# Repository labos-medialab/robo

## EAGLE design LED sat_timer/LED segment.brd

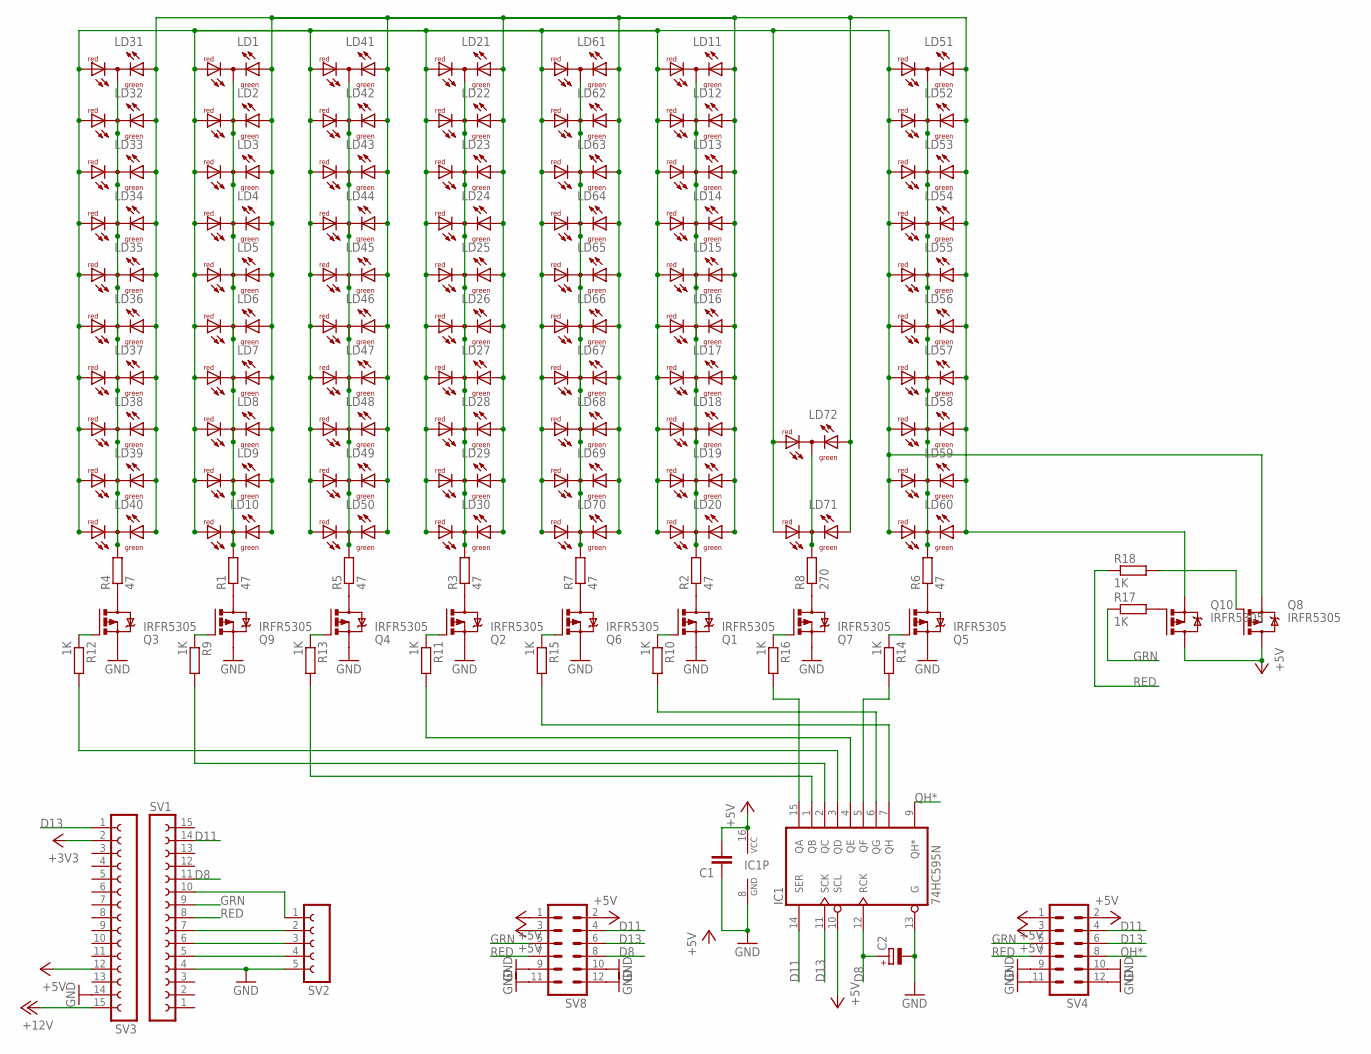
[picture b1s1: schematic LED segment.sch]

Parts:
C1: C-EU050-030X075; C050-030X075
C2: CPOL-EUE2.5-7; E2,5-7
IC1: 74HC595N; DIL16
LD1, LD2, LD3, LD4, LD5, LD6, LD7, LD8, LD9, LD10, LD11, LD12, LD13, LD14, LD15, LD16, LD17, LD18, LD19, LD20, LD21, LD22, LD23, LD24, LD25, LD26, LD27, LD28, LD29, LD30, LD31, LD32, LD33, LD34, LD35, LD36, LD37, LD38, LD39, LD40, LD41, LD42, LD43, LD44, LD45, LD46, LD47, LD48, LD49, LD50, LD51, LD52, LD53, LD54, LD55, LD56, LD57, LD58, LD59, LD60, LD61, LD62, LD63, LD64, LD65, LD66, LD67, LD68, LD69, LD70, LD71, LD72: DUOLED-RG-C; DUOLED-C-5MM
Q1, Q2, Q3, Q4, Q5, Q6, Q7, Q8, Q9, Q10: IRFR5305; D-PAK_TO252AA
R1, R2, R3, R4, R5, R6: 47; 0204/7
R7: 47; 0207/5V
R8: 270; 0204/7
R9, R10, R11, R12, R13, R14, R15, R16, R17, R18: 1K; 0204/7
SV1, SV3: FE15-1; FE15
SV2: FE05-1
SV4, SV8: MA06-2

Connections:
+3V3: SV3.2
+5V: C1.2, IC1.10 (SCL), IC1.16 (VCC), Q8.4 (D), Q10.4 (D), SV3.12, SV4.1, SV4.2, SV4.3, SV8.1, SV8.2, SV8.3
+12V: SV3.15
D8: C2.+, IC1.12 (RCK), SV1.11, SV8.8
D11: IC1.14 (SER), SV1.14, SV4.4, SV8.4
D13: IC1.11 (SCK), SV3.1, SV4.6, SV8.6
GND: C1.1, C2.-, IC1.8 (GND), IC1.13 (G), Q1.3 (S), Q2.3 (S), Q3.3 (S), Q4.3 (S), Q5.3 (S), Q6.3 (S), Q7.3 (S), Q9.3 (S), SV1.4, SV2.5, SV3.14, SV4.9, SV4.10, SV4.11, SV4.12, SV8.9, SV8.10, SV8.11, SV8.12
GRN: R17.1, SV1.9, SV4.5, SV8.5
unnamed: IC1.7 (QH), R15.2
unnamed: LD1.C, LD2.C, LD3.C, LD4.C, LD5.C, LD6.C, LD7.C, LD8.C, LD9.C, LD10.C, R1.2
unnamed: IC1.5 (QF), R14.2
unnamed: Q9.4 (D), R1.1
unnamed: LD11.C, LD12.C, LD13.C, LD14.C, LD15.C, LD16.C, LD17.C, LD18.C, LD19.C, LD20.C, R2.2
unnamed: Q1.4 (D), R2.1
unnamed: Q2.4 (D), R3.1
unnamed: LD21.C, LD22.C, LD23.C, LD24.C, LD25.C, LD26.C, LD27.C, LD28.C, LD29.C, LD30.C, R3.2
unnamed: Q3.4 (D), R4.1
unnamed: Q4.4 (D), R5.1
unnamed: LD31.C, LD32.C, LD33.C, LD34.C, LD35.C, LD36.C, LD37.C, LD38.C, LD39.C, LD40.C, R4.2
unnamed: Q5.4 (D), R6.1
unnamed: Q6.4 (D), R7.1
unnamed: LD41.C, LD42.C, LD43.C, LD44.C, LD45.C, LD46.C, LD47.C, LD48.C, LD49.C, LD50.C, R5.2
unnamed: Q7.4 (D), R8.1
unnamed: LD51.C, LD52.C, LD53.C, LD54.C, LD55.C, LD56.C, LD57.C, LD58.C, LD59.C, LD60.C, R6.2
unnamed: LD1.AR, LD2.AR, LD3.AR, LD4.AR, LD5.AR, LD6.AR, LD7.AR, LD8.AR, LD9.AR, LD10.AR, LD11.AR, LD12.AR, LD13.AR, LD14.AR, LD15.AR, LD16.AR, LD17.AR, LD18.AR, LD19.AR, LD20.AR, LD21.AR, LD22.AR, LD23.AR, LD24.AR, LD25.AR, LD26.AR, LD27.AR, LD28.AR, LD29.AR, LD30.AR, LD31.AR, LD32.AR, LD33.AR, LD34.AR, LD35.AR, LD36.AR, LD37.AR, LD38.AR, LD39.AR, LD40.AR, LD41.AR, LD42.AR, LD43.AR, LD44.AR, LD45.AR, LD46.AR, LD47.AR, LD48.AR, LD49.AR, LD50.AR, LD51.AR, LD52.AR, LD53.AR, LD54.AR, LD55.AR, LD56.AR, LD57.AR, LD58.AR, LD59.AR, LD60.AR, LD61.AR, LD62.AR, LD63.AR, LD64.AR, LD65.AR, LD66.AR, LD67.AR, LD68.AR, LD69.AR, LD70.AR, LD71.AR, LD72.AR, Q8.3 (S)
unnamed: LD1.AX (AG), LD2.AX (AG), LD3.AX (AG), LD4.AX (AG), LD5.AX (AG), LD6.AX (AG), LD7.AX (AG), LD8.AX (AG), LD9.AX (AG), LD10.AX (AG), LD11.AX (AG), LD12.AX (AG), LD13.AX (AG), LD14.AX (AG), LD15.AX (AG), LD16.AX (AG), LD17.AX (AG), LD18.AX (AG), LD19.AX (AG), LD20.AX (AG), LD21.AX (AG), LD22.AX (AG), LD23.AX (AG), LD24.AX (AG), LD25.AX (AG), LD26.AX (AG), LD27.AX (AG), LD28.AX (AG), LD29.AX (AG), LD30.AX (AG), LD31.AX (AG), LD32.AX (AG), LD33.AX (AG), LD34.AX (AG), LD35.AX (AG), LD36.AX (AG), LD37.AX (AG), LD38.AX (AG), LD39.AX (AG), LD40.AX (AG), LD41.AX (AG), LD42.AX (AG), LD43.AX (AG), LD44.AX (AG), LD45.AX (AG), LD46.AX (AG), LD47.AX (AG), LD48.AX (AG), LD49.AX (AG), LD50.AX (AG), LD51.AX (AG), LD52.AX (AG), LD53.AX (AG), LD54.AX (AG), LD55.AX (AG), LD56.AX (AG), LD57.AX (AG), LD58.AX (AG), LD59.AX (AG), LD60.AX (AG), LD61.AX (AG), LD62.AX (AG), LD63.AX (AG), LD64.AX (AG), LD65.AX (AG), LD66.AX (AG), LD67.AX (AG), LD68.AX (AG), LD69.AX (AG), LD70.AX (AG), LD71.AX (AG), LD72.AX (AG), Q10.3 (S)
unnamed: LD61.C, LD62.C, LD63.C, LD64.C, LD65.C, LD66.C, LD67.C, LD68.C, LD69.C, LD70.C, R7.2
unnamed: LD71.C, LD72.C, R8.2
unnamed: IC1.1 (QB), R13.2
unnamed: Q9.1 (G), R9.1
unnamed: Q1.1 (G), R10.1
unnamed: Q2.1 (G), R11.1
unnamed: Q3.1 (G), R12.1
unnamed: Q4.1 (G), R13.1
unnamed: Q5.1 (G), R14.1
unnamed: Q6.1 (G), R15.1
unnamed: Q7.1 (G), R16.1
unnamed: IC1.15 (QA), R16.2
unnamed: IC1.6 (QG), R10.2
unnamed: IC1.4 (QE), R11.2
unnamed: IC1.3 (QD), R12.2
unnamed: IC1.2 (QC), R9.2
unnamed: Q10.1 (G), R17.2
unnamed: Q8.1 (G), R18.2
unnamed: SV1.7, SV2.2
unnamed: SV1.6, SV2.3
unnamed: SV1.5, SV2.4
unnamed: SV1.10, SV2.1
QH*: IC1.9 (QH*), SV4.8
RED: R18.1, SV1.8, SV4.7, SV8.7

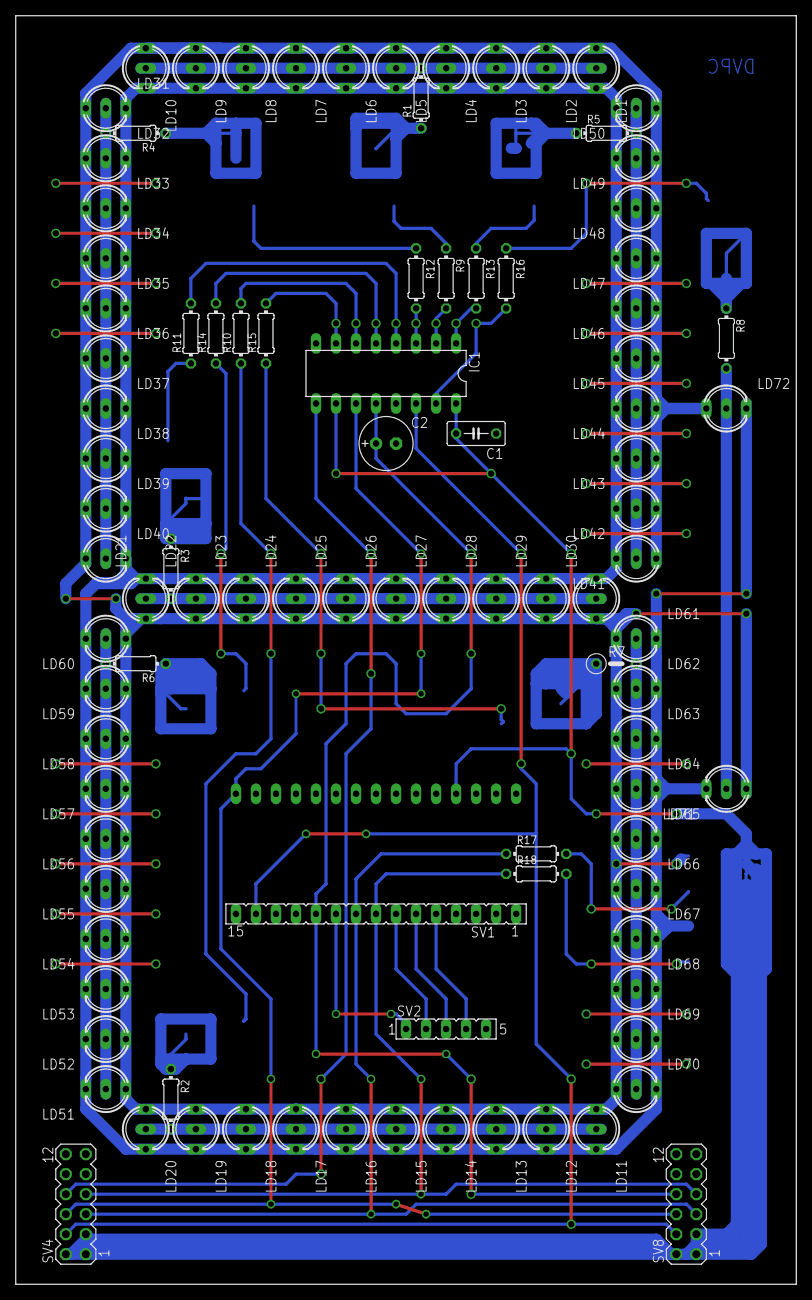
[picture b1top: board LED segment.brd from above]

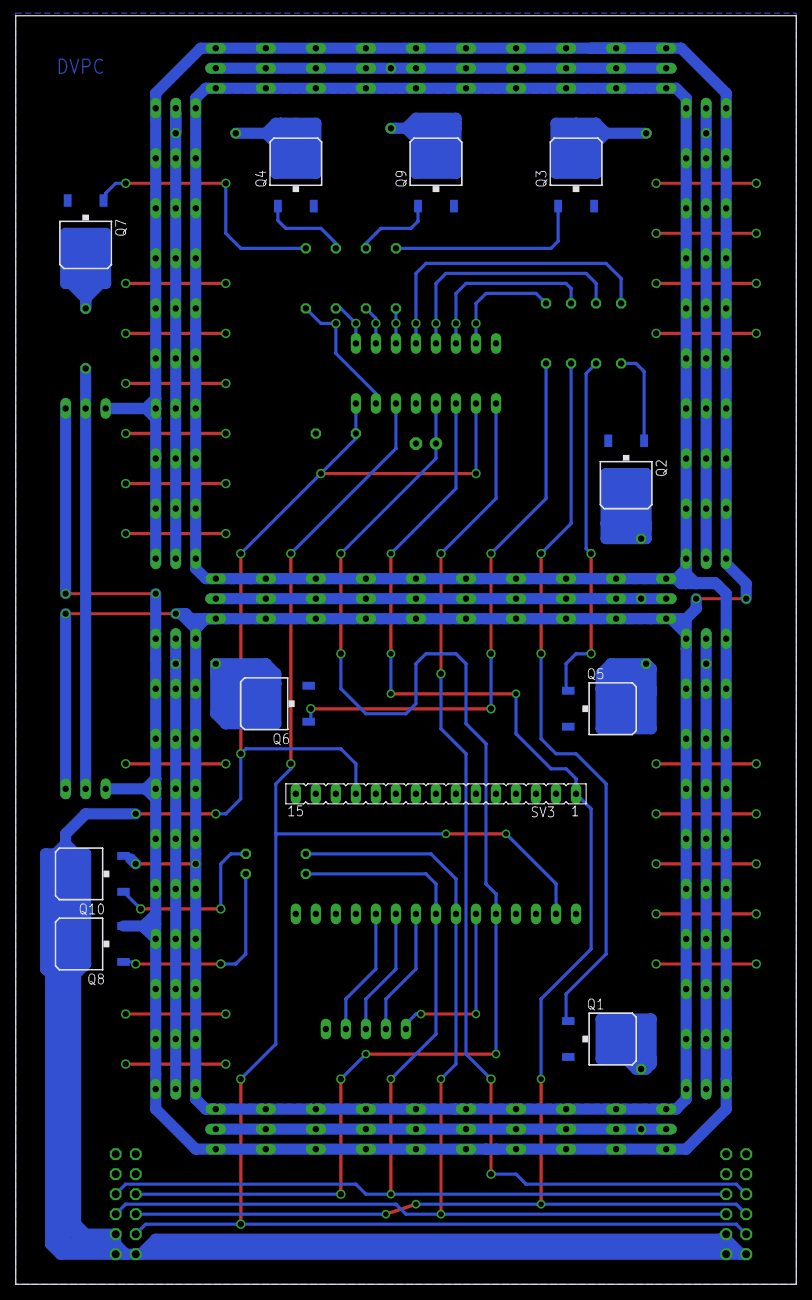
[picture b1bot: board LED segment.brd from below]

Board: 2 copper layers, 99.0 x 161.0 mm, 108 parts (11 on the bottom side), 48 nets.

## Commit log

2013-11-23 + ‘.sparkleshare’ + ‘SparkleShare.txt’
2013-11-23 + ‘testttt’
2013-11-23 / ‘testttt’
2013-11-23 + ‘bla blah blahž’
2013-11-23 / ‘bla blah blahž’
2013-11-23 - ‘SparkleShare.txt’ - ‘bla blah blahĹľ’ - ‘testttt’
2013-11-23 + ‘New Text Document.txt’
2013-11-23 < ‘New Text Document.txt’ > ‘la.txt’
2013-11-23 / ‘la.txt’
2013-11-23 < ‘la.txt’ > ‘New Text Document.txt’
2013-11-23 + ‘New Text Document (2).txt’
2013-11-23 < ‘New Text Document (2).txt’ > ‘.sparkleshare.txt’
2013-11-23 / ‘.sparkleshare.txt’
2013-11-23 / ‘New Text Document.txt’
2013-11-23 - ‘New Text Document.txt’
2013-11-23 + ‘ArduinoKodZaPrezentaciju/ArduinoKodZaPrezentaciju.ino’ + ‘HexRGB_to_IntRGB/HexRGB_to_IntRGB.ino’ + ‘Sensable/Sensable.ino’ + ‘akcelerometar/’ + ‘akcelerometar/akcelerometar.ino’ + ‘arduino_master/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
2013-11-28 + ‘Adxl345/ADXL345.cpp’ + ‘Adxl345/ADXL345.h’ + ‘Adxl345/License.txt’ + ‘BMP085/BMP085.cpp’ + ‘BMP085/BMP085.h’ + ‘BMP085/examples/Simple/Simple.ino’
2013-11-28 - ‘Adxl345/ADXL345.cpp’ - ‘Adxl345/ADXL345.h’ - ‘Adxl345/License.txt’ - ‘BMP085/BMP085.cpp’ - ‘BMP085/BMP085.h’ - ‘BMP085/examples/Simple/Simple.ino’
2013-11-28 + ‘Adxl345/’ + ‘Adxl345/ADXL345.cpp’ + ‘Adxl345/ADXL345.h’ + ‘Adxl345/License.txt’ + ‘BMP085/BMP085.cpp’ + ‘BMP085/BMP085.h’ + ‘BMP085/examples/Simple/Simple.ino’
2013-11-29 / ‘roboprojekt/roboprojekt.ino’
2013-12-09 + ‘LED_sat_timer/LED_sat_timer.ino’
2013-12-09 / ‘LED_sat_timer/LED_sat_timer.ino’
2014-01-02 + ‘prskalice/prskalice.ino’
2014-01-02 / ‘prskalice/prskalice.ino’
2014-01-03 + ‘LED sat_timer/LED segment.b#1’ + ‘LED sat_timer/LED segment.b#2’ + ‘LED sat_timer/LED segment.b#3’ + ‘LED sat_timer/LED segment.b#4’ + ‘LED sat_timer/LED segment.b#5’ + ‘LED sat_timer/LED segment.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
2014-01-31 + ‘myBridge/myBridge.ino’
2014-02-01 + ‘myBridge/myBridge_ino/myBridge_ino.ino’
2014-02-01 - ‘myBridge/myBridge_ino/myBridge_ino.ino’
2014-02-01 / ‘myBridge/myBridge.ino’
2014-02-15 + ‘New folder/’
2014-03-24 + ‘New folder (2)/’
2014-03-24 < ‘New folder (2)/’ > ‘mathos/’
2014-03-24 + ‘mathos/dz2.cpp’
2014-03-24 Update dz2.cpp
    hoće li skriptruner radit to?
2014-03-24 / ‘mathos/dz2.cpp’
2014-03-24 + ‘mathos/dz2 - Copy.cpp’
2014-03-24 < ‘mathos/dz2 - Copy.cpp’ > ‘mathos/dz2 .1.cpp’
2014-03-24 / ‘mathos/dz2 .1.cpp’
2014-03-24 < ‘mathos/dz2 .1.cpp’ > ‘mathos/dz2.1.cpp’
2014-03-24 < ‘mathos/dz2 - Copy.cpp’ > ‘mathos/dz2.2.cpp’
2014-03-24 / ‘mathos/dz2.2.cpp’
2014-03-25 + ‘mathos/dz2.2 - Copy.cpp’
2014-03-25 < ‘mathos/dz2.2 - Copy.cpp’ > ‘mathos/dz2.3.cpp’
2014-03-25 / ‘mathos/dz2.3.cpp’
2014-04-01 < ‘mathos/dz2 - Copy.cpp’ > ‘mathos/dz3.cpp’
2014-04-01 / ‘mathos/dz3.cpp’
2014-04-08 + ‘mathos/dz3 - Copy.cpp’
2014-04-08 < ‘mathos/dz3 - Copy.cpp’ > ‘mathos/dz4.cpp’
2014-04-08 / ‘mathos/dz4.cpp’
2014-04-08 + ‘mathos/dz4 - Copy.cpp’
2014-04-08 < ‘mathos/dz4 - Copy.cpp’ > ‘mathos/dz4.2.cpp’
2014-04-08 / ‘mathos/dz4.2.cpp’
2014-04-08 - ‘mathos/dz4.2.cpp’
2014-04-22 < ‘mathos/dz4 - Copy.cpp’ > ‘mathos/dz5.cpp’
2014-04-22 / ‘mathos/dz5.cpp’
2014-04-23 + ‘mathos/dz5 - Copy.cpp’
2014-04-23 < ‘mathos/dz5 - Copy.cpp’ > ‘mathos/dz5 .1.cpp’
2014-04-23 + ‘mathos/dz5 .1 - Copy.cpp’
2014-04-23 < ‘mathos/dz5 .1 - Copy.cpp’ > ‘mathos/dz5.2.cpp’
2014-04-23 < ‘mathos/dz5 .1.cpp’ > ‘mathos/dz5.1.cpp’
2014-04-23 < ‘mathos/dz5.cpp’ > ‘mathos/dz5.0.cpp’
2014-04-23 / ‘mathos/dz5.1.cpp’
2014-04-23 / ‘mathos/dz5.2.cpp’
2014-05-03 + ‘mathos/dz5.2 - Copy.cpp’
2014-05-03 < ‘mathos/dz5.2 - Copy.cpp’ > ‘mathos/dz6.z1.cpp’
2014-05-03 / ‘mathos/dz6.z1.cpp’
2014-05-03 < ‘mathos/dz6.z1.cpp’ > ‘mathos/dz6z1.cpp’
2014-05-04 / ‘mathos/dz6z1.cpp’
2014-05-07 + ‘mathos/dz6z1 - Shortcut.lnk’
2014-05-07 < ‘mathos/dz6z1 - Shortcut.lnk’ > ‘mathos/dz6z2.lnk’
2014-05-07 - ‘mathos/dz6z2.lnk’
2014-05-07 + ‘mathos/dz6z1 - Copy.cpp’
2014-05-07 < ‘mathos/dz6z1 - Copy.cpp’ > ‘mathos/dz6z2.cpp’
2014-05-07 / ‘mathos/dz6z2.cpp’
2014-05-07 + ‘mathos/dz6z2 - Copy.cpp’
2014-05-07 < ‘mathos/dz6z2 - Copy.cpp’ > ‘mathos/dz6z2_1.cpp’
2014-05-07 / ‘mathos/dz6z2_1.cpp’
2014-05-07 + ‘mathos/dz6z2_1 - Copy.cpp’
2014-05-07 < ‘mathos/dz6z2_1 - Copy.cpp’ > ‘mathos/dz6z2_2.cpp’
2014-05-07 / ‘mathos/dz6z2_2.cpp’
2014-05-07 + ‘mathos/dz6z1 - Copy (2).cpp’ + ‘mathos/dz6z1 - Copy (3).cpp’ + ‘mathos/dz6z1 - Copy (4).cpp’ + ‘mathos/dz6z1 - Copy.cpp’
2014-05-07 < ‘mathos/dz6z1 - Copy (2).cpp’ > ‘mathos/dz6z1_1.cpp’
2014-05-07 < ‘mathos/dz6z1 - Copy (3).cpp’ > ‘mathos/dz6z1_2.cpp’
2014-05-07 < ‘mathos/dz6z1 - Copy (4).cpp’ > ‘mathos/dz6z1_3.cpp’
2014-05-07 < ‘mathos/dz6z1 - Copy.cpp’ > ‘mathos/dz6z1_4.cpp’
2014-05-07 / ‘mathos/dz6z1_2.cpp’
2014-05-07 / ‘mathos/dz6z1_1.cpp’ / ‘mathos/dz6z1_3.cpp’ / ‘mathos/dz6z1_4.cpp’
2014-05-07 / ‘mathos/dz6z1_2.cpp’ / ‘mathos/dz6z1_4.cpp’
2014-05-07 / ‘mathos/dz6z1_1.cpp’ / ‘mathos/dz6z1_3.cpp’
2014-05-07 / ‘mathos/dz6z1_1.cpp’
2014-05-07 / ‘mathos/dz6z1_1.cpp’ / ‘mathos/dz6z1_4.cpp’
2014-05-07 / ‘mathos/dz6z1_1.cpp’ / ‘mathos/dz6z1_2.cpp’ / ‘mathos/dz6z1_3.cpp’
2014-05-07 / ‘mathos/dz6z1_3.cpp’
2014-05-07 / ‘mathos/dz6z1_4.cpp’
2014-05-12 < ‘mathos/dz6z1 - Copy.cpp’ > ‘mathos/dz7z1.cpp’
2014-05-12 / ‘mathos/dz7z1.cpp’
2014-05-12 + ‘mathos/dz7z1 - Copy.cpp’
2014-05-12 < ‘mathos/dz7z1 - Copy.cpp’ > ‘mathos/dz7z2.cpp’
2014-05-12 / ‘mathos/dz7z2.cpp’
2014-05-14 + ‘mathos/dz7z2 - Copy.cpp’
2014-05-14 < ‘mathos/dz7z2 - Copy.cpp’ > ‘mathos/dz7z3.cpp’
2014-05-14 / ‘mathos/dz7z3.cpp’
